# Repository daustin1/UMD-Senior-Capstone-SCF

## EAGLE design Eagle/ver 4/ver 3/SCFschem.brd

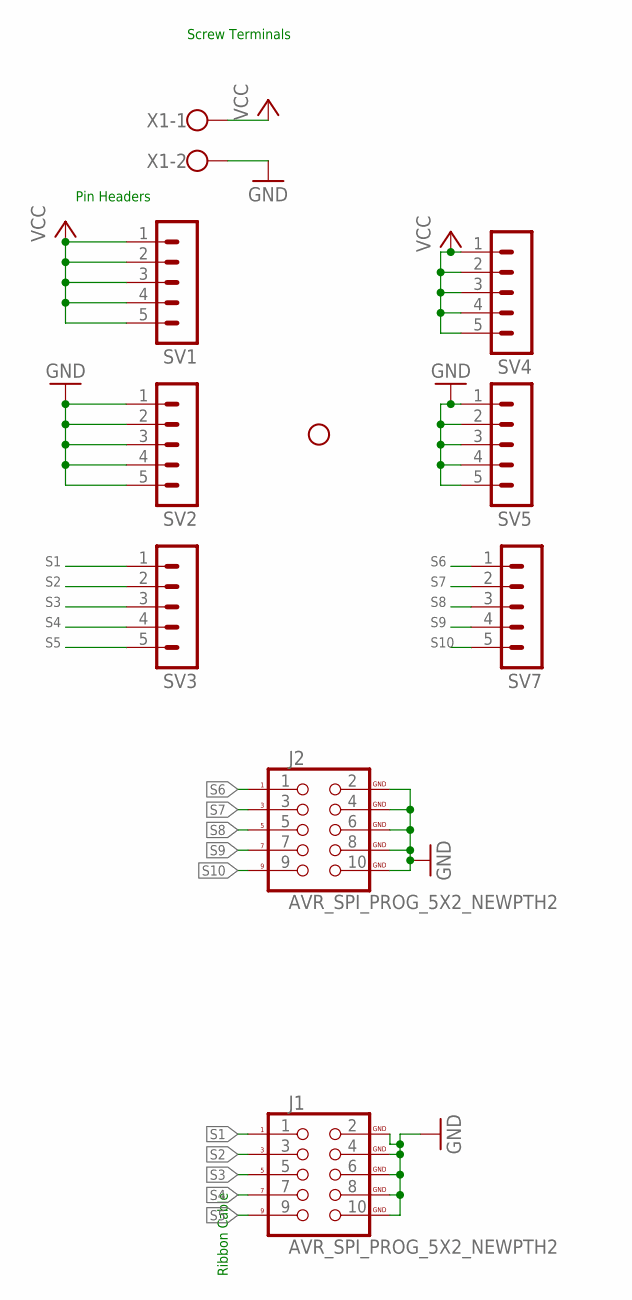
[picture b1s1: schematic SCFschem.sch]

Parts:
H1: STAND-OFF-NEWNEW; STAND-OFF-NEW
J1, J2: AVR_SPI_PROG_5X2_NEWPTH2; 2X5-SHROUDED
SV1, SV2, SV3, SV4, SV5, SV7: MA05-1
X1: 1X02_5MM_SCREW; W237-102

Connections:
GND: J1.2 (GND), J1.4 (GND), J1.6 (GND), J1.8 (GND), J1.10 (GND), J2.2 (GND), J2.4 (GND), J2.6 (GND), J2.8 (GND), J2.10 (GND), SV2.1, SV2.2, SV2.3, SV2.4, SV2.5, SV5.1, SV5.2, SV5.3, SV5.4, SV5.5, X1.2
S1: J1.1, SV3.1
S2: J1.3, SV3.2
S3: J1.5, SV3.3
S4: J1.7, SV3.4
S5: J1.9, SV3.5
S6: J2.1, SV7.1
S7: J2.3, SV7.2
S8: J2.5, SV7.3
S9: J2.7, SV7.4
S10: J2.9, SV7.5
VCC: SV1.1, SV1.2, SV1.3, SV1.4, SV1.5, SV4.1, SV4.2, SV4.3, SV4.4, SV4.5, X1.1

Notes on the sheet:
Screw Terminals
Ribbon Cable
Pin Headers

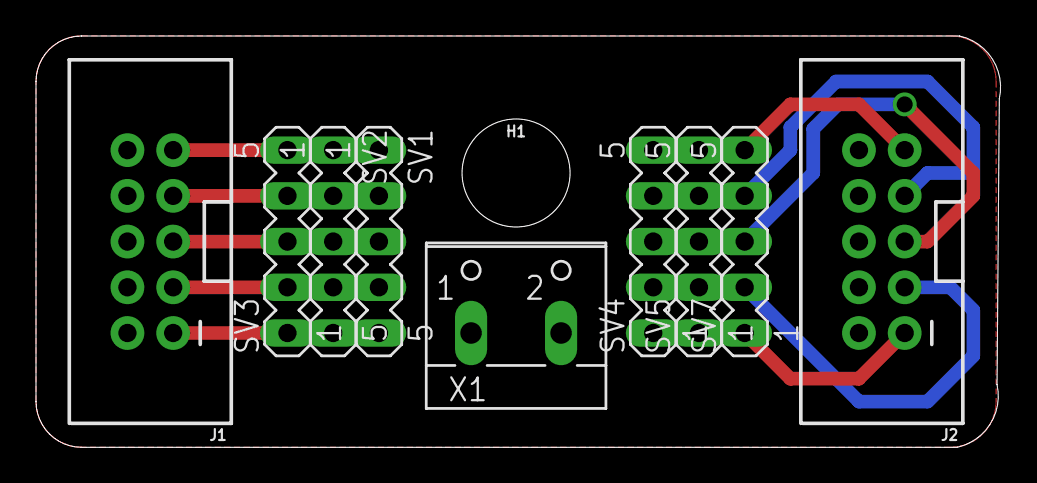
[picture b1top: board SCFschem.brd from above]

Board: 2 copper layers, 53.6 x 22.8 mm, 10 parts (0 on the bottom side), 12 nets.

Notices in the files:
parts and their libraries:
SparkFun-Connectors: Licensing: Creative Commons ShareAlike 4.0 International - https://creativecommons.org/licenses/by-sa/4.0
